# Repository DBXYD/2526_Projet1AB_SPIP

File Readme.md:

# 🐿️ Projet PAMI - Spip  (Coupe de France de Robotique)

##  Présentation de la Coupe
La **Coupe de France de Robotique** (Eurobot Open France) est une compétition annuelle organisée par **Planète Sciences**.  
Elle réunit des équipes étudiantes, associatives ou indépendantes, qui conçoivent des **robots autonomes** capables de relever des défis techniques en lien avec un thème annuel.
Depuis **plus de 10 ans**, l’association **ARES (Association de Robotique de l’ENSEA)** participe chaque année à cette compétition.  
En **2026**, la compétition se déroulera dans le cadre de la **33ᵉ édition des Rencontres de Robotique**.  
Le thème choisi est :  
> **« Winter is coming »**
Les robots auront 100 secondes pour réaliser un maximum d’actions sur une aire de jeu commune de 3 m x 2 m.
## Règlement
Le règlement complet est disponible sur le site officiel ([coupederobotique.fr](https://www.coupederobotique.fr/)), mais voici un résumé des grandes lignes :
### Aire du jeu 
Voici l’aire du jeu officielle de la Coupe de France de Robotique 2026 :

Légende :
1. Nid des écureuils  
2. Aires de départ PAMI dans le grenier  
3. Frigo  
4. Zone de chargement  
5. Zone de ramassage  
6. Garde-manger  
7. Thermomètre  
8. Curseur
### 🔹 Objectifs du thème
Les robots doivent aider les écureuils à stocker et protéger leurs noisettes en réalisant différentes actions :

1. **Gardons les noisettes au chaud !**  
   Ramasser les caisses de noisettes et les déposer dans un **garde-manger** ou dans le **nid**.  
   
2. **Trouver, c’est garder !**  
   Utiliser un petit actionneur mobile (PAMI) pour vider les **frigos** du grenier et les remplir avec des **caisses pourries**.  
   
3. **Pas trop chaud, ni trop froid.**  
   Déplacer le **curseur du thermomètre** pour régler la température au plus près du centre.  
   
4. **On est mieux dans son nid.**  
   Finir le match avec le **robot principal dans le nid**.  
   
5. **À table !**  
   Les petits écureuils (PAMIs) doivent rejoindre les **garde-mangers** et « manger » les noisettes.

Voici l'organisation principale du projet :

* 📁 **[Firmware](./Firmware/)** : Contient le code embarqué pour les microcontrôleurs, incluant l'asservissement.
* 📁 **[Hardware](./Hardware/)** : Regroupe les conceptions électroniques (PCB) et les modélisations mécaniques (3D).
* 📁 **[Datasheets](./Datasheets/)** : Contient l’ensemble des datasheets des différents composants utilisés.
* 📁 **[Strategie](./Strategie/)** : Documents et algorithmes définissant le comportement du robot pendant les matchs.
* 📁 **[Tableau de bord](./Tableau%20de%20bord/)** : Outils de monitoring et suivi des indicateurs de l'équipe.

# Rapport de projet - SPIP

## 1. Introduction

Le projet SPIP consiste à concevoir un robot PAMI pour la Coupe de France de Robotique. Le robot doit être autonome, compact, capable de se déplacer de manière contrôlée, d'interagir avec le terrain, d'éviter les obstacles et de réaliser des actions simples pendant le match.

Notre travail a donc porté sur trois grands axes :

- le choix et l'intégration des composants ;
- la conception électronique du robot avec KiCad ;
- le développement du firmware embarqué sur STM32.

Le robot est organisé autour d'une carte électronique principale. Cette carte relie le microcontrôleur, les moteurs, les encodeurs, les capteurs, les boutons, les LEDs, le connecteur de programmation et l'actionneur XL-320.

## 2. Objectif global du robot

Le robot doit pouvoir se déplacer de façon autonome sur l'aire de jeu de la Coupe de France de Robotique. Pour cela, nous avons besoin :

- d'un cerveau capable de piloter tous les périphériques ;
- de deux moteurs ;
- d'encodeurs pour connaître le déplacement réel ;
- d'un capteur ultrason pour détecter les obstacles ;
- d'un suiveur de ligne infrarouge pour corriger la trajectoire ;
- d'un servomoteur XL-320 pour actionner une partie mobile ;
- d'une carte électronique pour relier tous les éléments.

L'architecture générale est la suivante :

```mermaid
flowchart TD
    Batterie["+6 V batterie"] -->|Alimentation puissance +6 V| Driver["DRV8411<br/>Driver moteurs"]
    Batterie -->|Alimentation puissance +6 V| XL320["Dynamixel XL-320<br/>Actionneur"]
    Batterie -->|Entrée alimentation| Regulateur["Régulateur AZ1117<br/>3.3 V"]

    Regulateur -->|Alimentation logique 3.3 V| STM32["STM32G431CBU6<br/>Microcontrôleur"]
    Regulateur -->|Alimentation capteurs 3.3 V| Capteurs["Capteurs<br/>IR / ultrason / boutons / LEDs"]

    STM32 -->|Commandes PWM<br/>AIN1, AIN2, BIN1, BIN2| Driver
    Driver -->|Puissance moteur<br/>AOUT / BOUT| Moteurs["2 moteurs DC"]

    Moteurs -->|Rotation mesurée| Encodeurs["Encodeurs moteurs"]
    Encodeurs -->|Retour position / vitesse<br/>signaux A et B| STM32

    Capteurs -->|Informations terrain<br/>ligne, obstacle, boutons| STM32
    STM32 -->|UART half-duplex<br/>DATA| XL320

    STLINK["Connecteur STDC14<br/>ST-Link"] -->|Programmation / debug<br/>SWDIO, SWCLK, UART| STM32

    classDef power fill:#fff3cd,stroke:#f59f00,stroke-width:2px,color:#111;
    classDef logic fill:#dbeafe,stroke:#2563eb,stroke-width:2px,color:#111;
    classDef command fill:#fee2e2,stroke:#dc2626,stroke-width:2px,color:#111;
    classDef sensor fill:#dcfce7,stroke:#16a34a,stroke-width:2px,color:#111;
    classDef debug fill:#f3e8ff,stroke:#9333ea,stroke-width:2px,color:#111;

    class Batterie,Regulateur power;
    class STM32 logic;
    class Driver,Moteurs command;
    class Encodeurs,Capteurs sensor;
    class XL320,STLINK debug;

    linkStyle 0 stroke:#f59f00,stroke-width:2px;
    linkStyle 1 stroke:#f59f00,stroke-width:2px;
    linkStyle 2 stroke:#f59f00,stroke-width:2px;
    linkStyle 3 stroke:#2563eb,stroke-width:2px;
    linkStyle 4 stroke:#2563eb,stroke-width:2px;
    linkStyle 5 stroke:#dc2626,stroke-width:2px;
    linkStyle 6 stroke:#dc2626,stroke-width:2px;
    linkStyle 7 stroke:#16a34a,stroke-width:2px;
    linkStyle 8 stroke:#16a34a,stroke-width:2px;
    linkStyle 9 stroke:#16a34a,stroke-width:2px;
    linkStyle 10 stroke:#9333ea,stroke-width:2px;
    linkStyle 11 stroke:#9333ea,stroke-width:2px;
```

**Légende des liens :**

<div style="display: flex; flex-direction: column; gap: 6px; margin-top: 8px;">

<div style="background-color: #fff3cd; border-left: 6px solid #f59f00; padding: 8px;">
<strong>Orange</strong> : alimentation puissance <code>+6 V</code>.
</div>

<div style="background-color: #dbeafe; border-left: 6px solid #2563eb; padding: 8px;">
<strong>Bleu</strong> : alimentation logique <code>3.3 V</code>.
</div>

<div style="background-color: #fee2e2; border-left: 6px solid #dc2626; padding: 8px;">
<strong>Rouge</strong> : commande moteur et puissance moteur.
</div>

<div style="background-color: #dcfce7; border-left: 6px solid #16a34a; padding: 8px;">
<strong>Vert</strong> : retours capteurs et encodeurs vers le STM32.
</div>

<div style="background-color: #f3e8ff; border-left: 6px solid #9333ea; padding: 8px;">
<strong>Violet</strong> : programmation, debug et communication série.
</div>

</div>

## 3. Choix des composants

> **Note de conception :** Pour consulter l'inventaire complet du matériel et le détail des calculs de dimensionnement (calculs de puissance, choix des tailles de boîtiers CMS, etc.), reportez-vous au [Document de détails](./Hardware/details.md).

### 3.1 Microcontrôleur STM32G431CBU6

Nous avons choisi le **STM32G431CBU6** comme microcontrôleur principal du robot.

Datasheet : [Datasheet officielle STMicroelectronics](https://www.st.com/resource/en/datasheet/stm32g431cb.pdf)

Ce composant a été choisi car il correspond bien aux besoins du robot :

- il fonctionne en logique **3.3 V**, ce qui est adapté à notre circuit ;
- il dispose de nombreux GPIO pour connecter les capteurs, boutons, LEDs et signaux moteurs ;
- il intègre plusieurs timers, indispensables pour générer des signaux PWM et lire les encodeurs ;
- il possède des interfaces UART, utiles pour communiquer avec le XL-320 et avec le ST-Link ;
- son cœur ARM Cortex-M4 à 170 MHz offre assez de puissance pour faire tourner l'asservissement, la stratégie et les capteurs en parallèle.

Dans notre projet, le STM32 sert donc de centre de décision. Il lit les capteurs, calcule les consignes de mouvement, pilote les moteurs et exécute la stratégie de match.

### 3.2 Driver moteur DRV8411APWPR

Pour piloter les deux moteurs DC, nous avons utilisé un **DRV8411APWPR**.

Datasheet : [Datasheet Texas Instruments DRV8411](https://www.ti.com/lit/ds/symlink/drv8411.pdf)

Le STM32 ne peut pas alimenter directement les moteurs, car ses broches ne fournissent pas assez de courant. Le DRV8411 joue donc le rôle d'interface de puissance entre le microcontrôleur et les moteurs.

Nous l'avons choisi car :

- il permet de piloter deux moteurs DC avec un seul circuit ;
- il fonctionne avec des signaux logiques compatibles avec le STM32 ;
- il accepte une alimentation moteur séparée, ici le rail **+6 V** ;
- il possède une sortie de défaut, notée `FAULT`, permettant au microcontrôleur de détecter un problème ;
- il peut être commandé par des signaux PWM pour régler la vitesse.

Dans le schéma KiCad, les signaux importants sont :

- `AIN1` et `AIN2` pour le moteur A ;
- `BIN1` et `BIN2` pour le moteur B ;
- `AOUT1`, `AOUT2`, `BOUT1`, `BOUT2` vers les connecteurs moteurs ;
- `FAULT` vers le STM32 ;
- `AIPROPI` et `BIPROPI` avec des résistances pour la partie mesure/protection du driver.

### 3.3 Moteurs DC avec encodeurs

Le robot utilise deux moteurs DC avec encodeurs intégrés.

Dans le schéma KiCad, les connecteurs moteurs sont des connecteurs JST 6 broches :

- `J6` pour un moteur ;
- `J7` pour l'autre moteur.

Chaque connecteur transporte :

- les deux sorties moteur venant du driver ;
- l'alimentation de l'encodeur ;
- la masse ;
- les deux signaux encodeur A et B.

Nous avons choisi des moteurs avec encodeurs car un simple moteur DC ne permet pas de connaître la distance réelle parcourue. Avec les encodeurs, le STM32 peut compter les impulsions et en déduire :

- la distance parcourue ;
- la vitesse réelle ;
- le sens de rotation ;
- l'erreur entre la consigne et le mouvement réel.

Cela permet de faire un asservissement et d'obtenir des déplacements plus précis.

### 3.4 Servomoteur Dynamixel XL-320

Le robot utilise un **Dynamixel XL-320** comme actionneur pour une partie mobile, notamment la queue.

Datasheet : [Documentation ROBOTIS officielle](https://emanual.robotis.com/docs/en/dxl/x/xl320/)

Nous avons choisi le XL-320 car c'est un servomoteur intelligent. Contrairement à un servo simple, il intègre déjà :

- un moteur ;
- un contrôleur ;
- une électronique de puissance ;
- un protocole de communication ;
- un retour d'état.

Il se commande avec une liaison série half-duplex. Dans KiCad, il est relié par le connecteur `J3`, avec :

- `+6V` pour l'alimentation ;
- `GND` ;
- `DATA` pour la communication.

Dans le `.ioc`, la broche `PC4` est configurée en `USART1` half-duplex pour communiquer avec le XL-320.

### 3.5 Capteur ultrason HC-SR04

Le capteur ultrason est utilisé pour détecter les obstacles devant le robot.

Datasheet : [Datasheet HC-SR04 via DigiKey](https://www.digikey.com/en/htmldatasheets/production/3822706/0/0/1/hc-sr04.html)

Nous l'avons ajouté pour que le robot puisse s'arrêter lorsqu'un objet ou un autre robot se trouve trop près. Le principe est simple :

- le STM32 envoie une impulsion sur `TRIG` ;
- le capteur émet une onde ultrasonore ;
- le signal `ECHO` reste actif pendant une durée proportionnelle à la distance ;
- le STM32 mesure cette durée et calcule la distance.

Dans KiCad, le capteur est relié au connecteur `J4` :

- `+3.3V` ;
- `TRIGG` ;
- `ECHO` ;
- `GND`.

Dans le code, si la distance mesurée est inférieure à 10 cm, le robot met les deux vitesses moteur à zéro. Cela permet d'éviter une collision.

### 3.6 Suiveur de ligne infrarouge

Le suiveur de ligne infrarouge est utilisé pour détecter la position du robot par rapport à une ligne au sol.

Dans KiCad, le connecteur `J5` relie le module infrarouge au STM32 :

- `+3.3V` ;
- `X1` ;
- `X2` ;
- `X3` ;
- `X4` ;
- `GND`.

Nous avons choisi un suiveur de ligne à plusieurs sorties car il donne plus d'information qu'un seul capteur. Avec quatre signaux, le robot peut savoir si la ligne est :

- centrée ;
- décalée à gauche, légèrement ou fortement ;
- décalée à droite, légèrement ou fortement ;
- perdue ou détectée partiellement.

Dans le firmware, les valeurs des quatre capteurs sont combinées dans une variable `position`. Cette position peut ensuite être utilisée pour corriger la trajectoire du robot.

### 3.7 Régulateur AZ1117-3.3

Le régulateur **AZ1117-3.3** permet de créer le rail d'alimentation 3.3 V à partir de l'alimentation principale.

Datasheet : [Datasheet officielle AZ1117](https://www.diodes.com/assets/Datasheets/AZ1117.pdf)

Nous l'avons ajouté car le STM32 et plusieurs signaux logiques doivent être alimentés en 3.3 V, alors que la partie puissance du robot fonctionne avec une tension plus élevée, notamment le rail +6 V.

Dans KiCad, le régulateur est accompagné de condensateurs de découplage et de stabilisation. Ces condensateurs servent à limiter les variations de tension et à rendre l'alimentation plus stable.

### 3.8 Condensateurs de découplage

Le schéma KiCad contient plusieurs condensateurs :

- `100nF` près des circuits intégrés ;
- `1uF`, `10uF` et `22uF` pour stabiliser les rails d'alimentation ;
- des condensateurs autour du driver moteur et du régulateur.

Datasheets :

- [Wurth 100 nF 885012205085](https://www.we-online.com/components/products/datasheet/885012205085.pdf)
- [Wurth 10 nF 885012205067](https://www.we-online.com/components/products/datasheet/885012205067.pdf)
- [Wurth 1 uF 885012206076](https://www.we-online.com/components/products/datasheet/885012206076.pdf)
- [Wurth 22 uF 885012107019](https://www.we-online.com/components/products/datasheet/885012107019.pdf)

Ces condensateurs sont nécessaires car les moteurs et les circuits numériques peuvent créer des variations rapides de courant. Sans découplage, ces variations pourraient provoquer des resets du microcontrôleur ou des comportements instables.

### 3.9 Résistances

Le PCB utilise plusieurs résistances :

- résistances de tirage pour les boutons ;
- résistances en série avec les LEDs ;
- résistances liées au driver moteur ;
- résistance de `BOOT0` ;
- résistances de valeurs particulières comme `82k5`.

Datasheets :

- [Yageo RC0805 general purpose](https://www.yageo.com/upload/media/product/productsearch/datasheet/rchip/PYu-RC_Group_51_RoHS_L_12.pdf)
- [RS Pro 1 kOhm](https://docs.rs-online.com/21eb/0900766b8157cb45.pdf)

Les résistances de LEDs sont dimensionnées pour limiter le courant. Les annotations du schéma indiquent les tensions directes des LEDs, par exemple `1.7V @ 1mA`, `2.3V @ 1mA` ou `2.6V @ 1mA`. Le but est d'avoir des voyants visibles sans consommer trop de courant ni endommager les LEDs.

### 3.10 LEDs utilisateur

Le PCB contient plusieurs LEDs, reliées à des signaux comme :

- `LEDR` ;
- `LEDG` ;
- `LEDB`.

Datasheets :

- [LED rouge Wurth 150060RS55040](https://www.we-online.com/components/products/datasheet/150060RS55040.pdf)
- [LED verte Wurth 150060GS55040](https://www.we-online.com/components/products/datasheet/150060GS55040.pdf)
- [LED bleue Wurth 150060BS55040](https://www.we-online.com/components/products/datasheet/150060BS55040.pdf)

Nous les avons ajoutées pour faciliter les tests. Elles peuvent indiquer un état du robot, un mode de fonctionnement, une erreur ou une étape de stratégie.

### 3.11 Boutons utilisateur

Le PCB contient plusieurs boutons, associés aux signaux :

- `Button1` ;
- `Button2` ;
- `Button3`.

Ils permettent de déclencher manuellement des actions, de changer d'état ou de lancer une séquence de test. Dans le `.ioc`, ces boutons sont configurés en interruptions externes, ce qui permet au STM32 de réagir immédiatement à un appui.

### 3.12 Connecteur de programmation STDC14

Le connecteur `J2` est un connecteur **STDC14**. Il sert à programmer et déboguer le STM32 avec un ST-Link.

Documentation :

- [Documentation STDC14 / STLINK-V3](https://www.st.com/content/ccc/resource/technical/document/user_manual/group1/99/49/91/b6/b2/3a/46/e5/DM00526767/files/DM00526767.pdf/jcr:content/translations/en.DM00526767.pdf)

Il relie notamment :

- `SWDIO` ;
- `SWCLK` ;
- `NRST` ;
- `STLINK_TX` ;
- `STLINK_RX` ;
- `3.3V` ;
- `GND`.

Nous l'avons mis pour pouvoir flasher le programme, déboguer le code et utiliser une liaison UART avec l'ordinateur.

## 4. Explication du projet KiCad

Le projet KiCad se trouve dans :

- [Schéma KiCad](./Hardware/Kicad_SPIP/Kicad_SPIP.kicad_sch)
- [PCB KiCad](./Hardware/Kicad_SPIP/Kicad_SPIP.kicad_pcb)

Le schéma est organisé en blocs fonctionnels :

- alimentation générale ;
- STM32G431CBU6 ;
- driver + moteurs ;
- servo XL-320 ;
- ultrason ;
- infrarouge ;
- boutons ;
- LEDs ;
- programmateur ;
- trous de fixation.

Cette organisation permet de comprendre rapidement le rôle de chaque partie.

### 4.1 Bloc alimentation

Le bloc alimentation sépare deux niveaux de tension :

- `+6V` pour les éléments de puissance, comme les moteurs et le XL-320 ;
- `+3.3V` pour le STM32 et les signaux logiques.

Le régulateur transforme la tension principale en 3.3 V. Des condensateurs sont placés autour des rails d'alimentation pour éviter les chutes de tension lors des appels de courant.

### 4.2 Bloc STM32

Le STM32 est au centre du schéma. Les pins sont nommées selon leur rôle logiciel :

- `PA0-US_TRIG` ;
- `PA1-US_ECHO_INT` ;
- `PA4-X1_INT` à `PA7-X4_INT` ;
- `PC4-UART_XL320` ;
- `PB10-MotorFault` ;
- `PB4/PB5` pour l'encodeur du moteur A ;
- `PB6/PB7` pour l'encodeur du moteur B ;
- `PA15/PB3/PA9/PA10` pour les PWM moteur ;
- `PA13/PA14` pour le debug SWD.

Le fait de nommer les signaux directement dans KiCad rend le schéma plus lisible et facilite la correspondance avec le fichier `.ioc`.

### 4.3 Bloc driver moteur

Le bloc moteur contient le DRV8411 et les connecteurs moteurs. Le STM32 envoie des signaux PWM au driver, et le driver fournit le courant aux moteurs.

Nous avons séparé la partie commande et la partie puissance :

- le STM32 commande avec des signaux logiques ;
- le driver gère le courant moteur ;
- les encodeurs renvoient l'information de mouvement au STM32.

Cette séparation est indispensable, car elle protège le microcontrôleur et permet un pilotage plus précis.

### 4.4 Bloc programmateur

Le connecteur STDC14 sert à relier le ST-Link pour flasher le programme et déboguer le code. 

Il permet d'accéder directement aux signaux de programmation `SWDIO` et `SWCLK`, ainsi qu'aux broches UART du STM32 pour envoyer des données vers l'ordinateur pendant les tests.

### 4.5 Bloc servomoteur intelligent

Ce bloc contient le connecteur pour le servomoteur Dynamixel XL-320. 

Le connecteur est relié au rail `+6V` pour la puissance et utilise la broche `PC4` configurée en UART half-duplex pour l'échange de données. Cette configuration permet de commander la position de l'actionneur avec un seul fil de signal.

### 4.6 Bloc capteurs

Le bloc capteurs regroupe l'ultrason et les capteurs infrarouges.

L'ultrason est utilisé pour l'évitement d'obstacles. Les capteurs infrarouges servent à suivre une ligne ou à détecter un décalage latéral.

Dans le PCB, ces capteurs sont connectés par des JST. Cela permet de démonter ou remplacer facilement un capteur sans ressouder la carte.

### 4.7 Bloc interface utilisateur

Les boutons et les LEDs permettent de tester le robot sans avoir besoin de modifier le code à chaque fois. Les boutons peuvent lancer des actions, et les LEDs peuvent afficher l'état du robot.

Ce bloc est utile pendant les phases de debug, car il donne un retour visuel immédiat.

### 4.8 Routage du PCB

Dans le PCB, les composants principaux sont placés de manière à limiter les longueurs de pistes :

- le STM32 est proche des signaux logiques ;
- le driver moteur est proche des connecteurs moteurs ;
- les connecteurs capteurs sont en bord de carte pour faciliter le câblage ;
- les trous de fixation permettent une intégration propre dans le châssis.

Les rails `GND`, `+3.3V` et `+6V` sont clairement séparés dans les nets KiCad. Cela permet de distinguer la puissance moteur de la logique microcontrôleur.
## 5. Configuration STM32CubeIDE et fichier `.ioc`

Le fichier de configuration est :

- [Firware_SPIP.ioc](./Firmware/Firware_SPIP/Firware_SPIP.ioc)

Ce fichier relie la conception électronique au code embarqué. Il indique quel pin du microcontrôleur correspond à chaque fonction.

### 5.1 Horloge

Le STM32 est configuré avec une fréquence système de **170 MHz**. Cette fréquence permet d'avoir assez de précision pour :

- les PWM moteurs ;
- la mesure ultrason ;
- les timers d'interruption ;
- l'asservissement.

### 5.2 TIM2 pour les PWM moteurs

Le timer `TIM2` est utilisé avec quatre canaux PWM :

- `TIM2_CH1` : `MotorA_PWM_Forward` ;
- `TIM2_CH2` : `MotorA_PWM_Reverse` ;
- `TIM2_CH3` : `MotorB_PWM_Forward` ;
- `TIM2_CH4` : `MotorB_PWM_Reverse`.

Ce choix permet de gérer le sens et la vitesse des deux moteurs. Chaque moteur a deux commandes, une pour le sens avant et une pour le sens arrière.

### 5.3 TIM3 et TIM4 pour les encodeurs

Les timers `TIM3` et `TIM4` sont configurés en mode encodeur :

- `TIM3` lit l'encodeur du moteur A ;
- `TIM4` lit l'encodeur du moteur B.

Le mode encodeur permet au microcontrôleur de compter automatiquement les impulsions A/B des encodeurs, ce qui donne une mesure fiable du mouvement.

### 5.4 TIM1 pour l'ultrason

Le timer `TIM1` est utilisé pour mesurer la durée du signal `ECHO` du capteur ultrason. Son prescaler permet d'obtenir une base de temps adaptée à la mesure en microsecondes.

Cette mesure est ensuite convertie en distance.

### 5.5 TIM6 comme ordonnanceur périodique

Le timer `TIM6` déclenche régulièrement une interruption. Dans cette interruption, le programme :

- déclenche l'ultrason ;
- met à jour le suiveur de ligne ;
- met à jour les encodeurs ;
- met à jour l'asservissement ;
- met à jour le mouvement ;
- remet périodiquement à zéro l'erreur cumulée du correcteur.

Cela permet de faire fonctionner plusieurs sous-systèmes en parallèle.

### 5.6 USART1 pour le XL-320

`USART1` est configuré en half-duplex sur `PC4`. Cela correspond au fonctionnement du XL-320, qui utilise une seule ligne de données pour envoyer et recevoir.

### 5.7 USART2 pour le ST-Link

`USART2` utilise `PA2` et `PA3`. Cette liaison peut servir au debug avec le ST-Link, par exemple pour afficher des informations sur un terminal série.

### 5.8 Interruptions externes

Plusieurs pins sont configurées en interruptions :

- `US_ECHO_INT` pour détecter les fronts du signal ultrason ;
- `MotorFault` pour détecter un problème driver ;
- les boutons utilisateur.

Les interruptions permettent de réagir rapidement à des événements sans attendre la boucle principale.

## 6. Explication du firmware

Le code embarqué se trouve dans :

- [Core/Src](./Firmware/Firware_SPIP/Core/Src)
- [Core/Inc](./Firmware/Firware_SPIP/Core/Inc)

Le firmware est séparé en modules. Chaque module gère une partie précise du robot.

### 6.1 `motor.c` et `motor.h`

Le module moteur gère le PWM appliqué aux moteurs. Il transforme une consigne de vitesse finale en rapport cyclique PWM.

Nous avons séparé ce module car le pilotage bas niveau des moteurs doit être indépendant de la stratégie. La stratégie dit au robot quoi faire, tandis que `motor.c` applique physiquement la puissance aux moteurs.

### 6.2 `encoder.c` et `encoder.h`

Le module encodeur lit les compteurs des timers en mode encodeur. Il calcule les variations de ticks entre deux appels.

Ces ticks sont essentiels pour connaître le mouvement réel. Sans encodeur, le robot pourrait dériver à cause des différences entre les moteurs, du frottement ou de la batterie.

### 6.3 `control.c` et `control.h`

Le module d'asservissement compare la vitesse demandée avec la vitesse mesurée par les encodeurs.

Le code calcule une erreur :

```c
error = control->ref_speed - 1000 * encoder->delta_ticks;
```

Puis il applique une correction proportionnelle et intégrale :

```c
motor->speed_final = control->ref_speed
                   + (control->Kp * error)
                   + (control->Ki * control->error_cumul);
```

Nous avons utilisé ce principe car les deux moteurs ne tournent jamais exactement pareil. L'asservissement permet de corriger les écarts et d'obtenir un mouvement plus régulier.

### 6.4 `move.c` et `move.h`

Le module mouvement gère les ordres de haut niveau :

- avancer d'une certaine distance ;
- tourner d'un certain angle ;
- s'arrêter ;
- s'arrêter en cas d'obstacle ultrason.

La fonction `move_forward` convertit une distance en centimètres en ticks encodeur. Pour cela, on utilise le périmètre de la roue :

```c
float perimeter_cm = 2.0f * M_PI * move->radius;
float K = encoder->cnt_tr / perimeter_cm;
move->d_target_cnt = d_target_cm * K;
```

Cette conversion permet de donner des ordres simples en centimètres tout en utilisant les encodeurs en interne.

### 6.5 Correction par suiveur de ligne

Le suiveur de ligne est lu régulièrement dans l'interruption du timer grâce à `LF_Update(&h_lineFollower)`. Cette fonction met à jour la position détectée par les quatre capteurs infrarouges.

Cette position est ensuite transmise à `move_update` grâce à l'appel suivant dans `main.c` :

```c
move_update(&move, &control_left, &control_right,
            &encoder_left, &encoder_right,
            &us_sensor, &h_lineFollower);
```

### 6.6 `Line_Follower.c` et `Line_Follower.h`

Le module suiveur de ligne lit les quatre entrées infrarouges :

```c
lf->position = lf->sensor_values[0] * 1000
             + lf->sensor_values[1] * 100
             + lf->sensor_values[2] * 10
             + lf->sensor_values[3];
```

Cette méthode permet de transformer quatre lectures digitales en une seule valeur facile à comparer. Par exemple :

- `0110` devient `110`, considéré comme centre ;
- `1000` indique une détection à gauche ;
- `0001` indique une détection à droite.

### 6.7 `Ultrasound.c` et `Ultrasound.h`

Le module ultrason gère le capteur HC-SR04. Il déclenche le capteur, mesure le temps du signal echo et calcule la distance.

Dans `move_update`, la sécurité obstacle est prioritaire :

```c
if (us_sensor->distance_cm > 0.0f && us_sensor->distance_cm < 10.0f) {
    control_set_speed(control_left, 0);
    control_set_speed(control_right, 0);
    return;
}
```

Nous avons fait cela pour que le robot s'arrête immédiatement si un obstacle est trop proche.

### 6.8 `xl320.c` et `xl320.h`

Le module XL-320 initialise et commande le servomoteur Dynamixel.

Dans `main.c`, le XL-320 est initialisé avec l'UART puis configuré :

```c
XL320_Init(&huart1);
XL320_Config_LowPower(254);
XL320_SetSpeed(254, 300);
```

L'identifiant `254` correspond à un broadcast, ce qui permet d'envoyer une commande à tous les servos connectés.

### 6.9 `strategy.c` et `strategy.h`

Le module stratégie définit plusieurs séquences d'actions : `strat_one`, `strat_two`, `strat_three`, `strat_four` et `strat_five`.

Chaque stratégie correspond à un enchaînement différent de déplacements. La fonction reçoit aussi une couleur, par exemple `"yellow"` ou `"blue"`, afin d'adapter le sens du virage selon le côté du terrain.

La stratégie utilisée actuellement dans `main.c` est :

```c
strat_two(&status, "yellow");
```

Nous avons choisi une machine à états car elle permet de décrire clairement la séquence de match. Chaque état correspond à une action précise : avancer, attendre la fin du déplacement, tourner, attendre la fin du virage, puis passer à l'action suivante.

### 6.10 `main.c`

Le fichier `main.c` initialise tous les modules :

- capteur ultrason ;
- suiveur de ligne ;
- moteurs ;
- encodeurs ;
- mouvement ;
- asservissement ;
- stratégie ;
- XL-320.

Avant d'entrer dans la boucle principale, le programme utilise aussi une condition de départ liée au capteur ultrason :

```c
while (us_sensor.distance_cm < 10) {
    US_Update(&us_sensor);
    HAL_Delay(50);
}
```

Cette partie joue le rôle de tirette ou de condition de départ : le robot attend que la distance mesurée soit suffisante avant de lancer sa stratégie.

La boucle principale appelle actuellement la stratégie `strat_two` avec la couleur `"yellow"`, ainsi que le mouvement de la queue :

```c
while (1)
{
    strat_two(&status, "yellow");
    move_tail(&status_tail);
}
```

La couleur passée à la fonction permet d'adapter le sens du virage selon le côté de départ du robot. Les mises à jour rapides sont faites dans l'interruption de `TIM6`, ce qui permet de garder un comportement régulier.

## 7. Résumé

Nous avons séparé le code en modules pour rendre le projet plus lisible et plus facile à tester.

Chaque fichier a une responsabilité :

- `motor` pilote le PWM ;
- `encoder` lit les ticks ;
- `control` fait l'asservissement ;
- `move` gère les distances et les rotations ;
- `Line_Follower` lit les capteurs IR ;
- `Ultrasound` mesure les distances ;
- `xl320` commande le servomoteur ;
- `strategy` décide les actions ;
- `main` initialise et orchestre le système.

Ce découpage évite d'avoir tout le code dans un seul fichier et facilite les corrections.

## 8. Conclusion

Le projet SPIP combine une partie électronique, une partie mécanique et une partie logicielle. La carte KiCad a été conçue pour centraliser les connexions du robot autour du STM32G431CBU6. Le choix des composants répond aux besoins principaux : puissance moteur, mesure de position, détection d'obstacle, suivi de ligne, communication avec le servomoteur et debug.

Le firmware transforme cette architecture matérielle en comportement autonome. Les encodeurs permettent de mesurer le mouvement, l'asservissement corrige les erreurs de vitesse, le suiveur infrarouge prépare la correction de trajectoire, l'ultrason évite les obstacles, et la stratégie enchaîne les actions du robot.

L'ensemble du travail permet d'obtenir une base de robot autonome capable de se déplacer, se corriger, réagir à son environnement et exécuter une séquence de match.

## 9. Demonstration

Voici une vidéo de notre PAMI se dirigeaant vers un des gardes manger

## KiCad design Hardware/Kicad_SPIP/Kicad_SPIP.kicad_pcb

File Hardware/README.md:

# ⚙️ Hardware & Conception

Ce dossier contient tous les éléments physiques de Spip.

## 🔌 Électronique
- **Alimentation** : Batterie Lipo (7.4V pour le XL320, régulé 3.3V pour le STM32).
- **Drivers** : Driver moteur DC (pont en H) et bus Dynamixel pour le XL320.
- **Schémas** : Voir le fichier `schema_cablage.pdf` dans ce dossier.

## 🔩 Mécanique
- **Châssis** : Découpe laser ou impression 3D.
- **Queue** : Pièce spécifique montée sur l'axe du XL320.
- **Roues** : 2 roues motrices + 1 roue folle à l'arrière.

## 📦 Liste de composants (BOM)
- 1x STM32G431CBU6
- 2x Moteurs à encodeurs
- 1x Robotis Dynamixel XL320
- 1x Capteur Ultrason HC-SR04 (ou équivalent)
- 1x Capteur de couleur
- 3x Capteurs de ligne (Infrarouge)

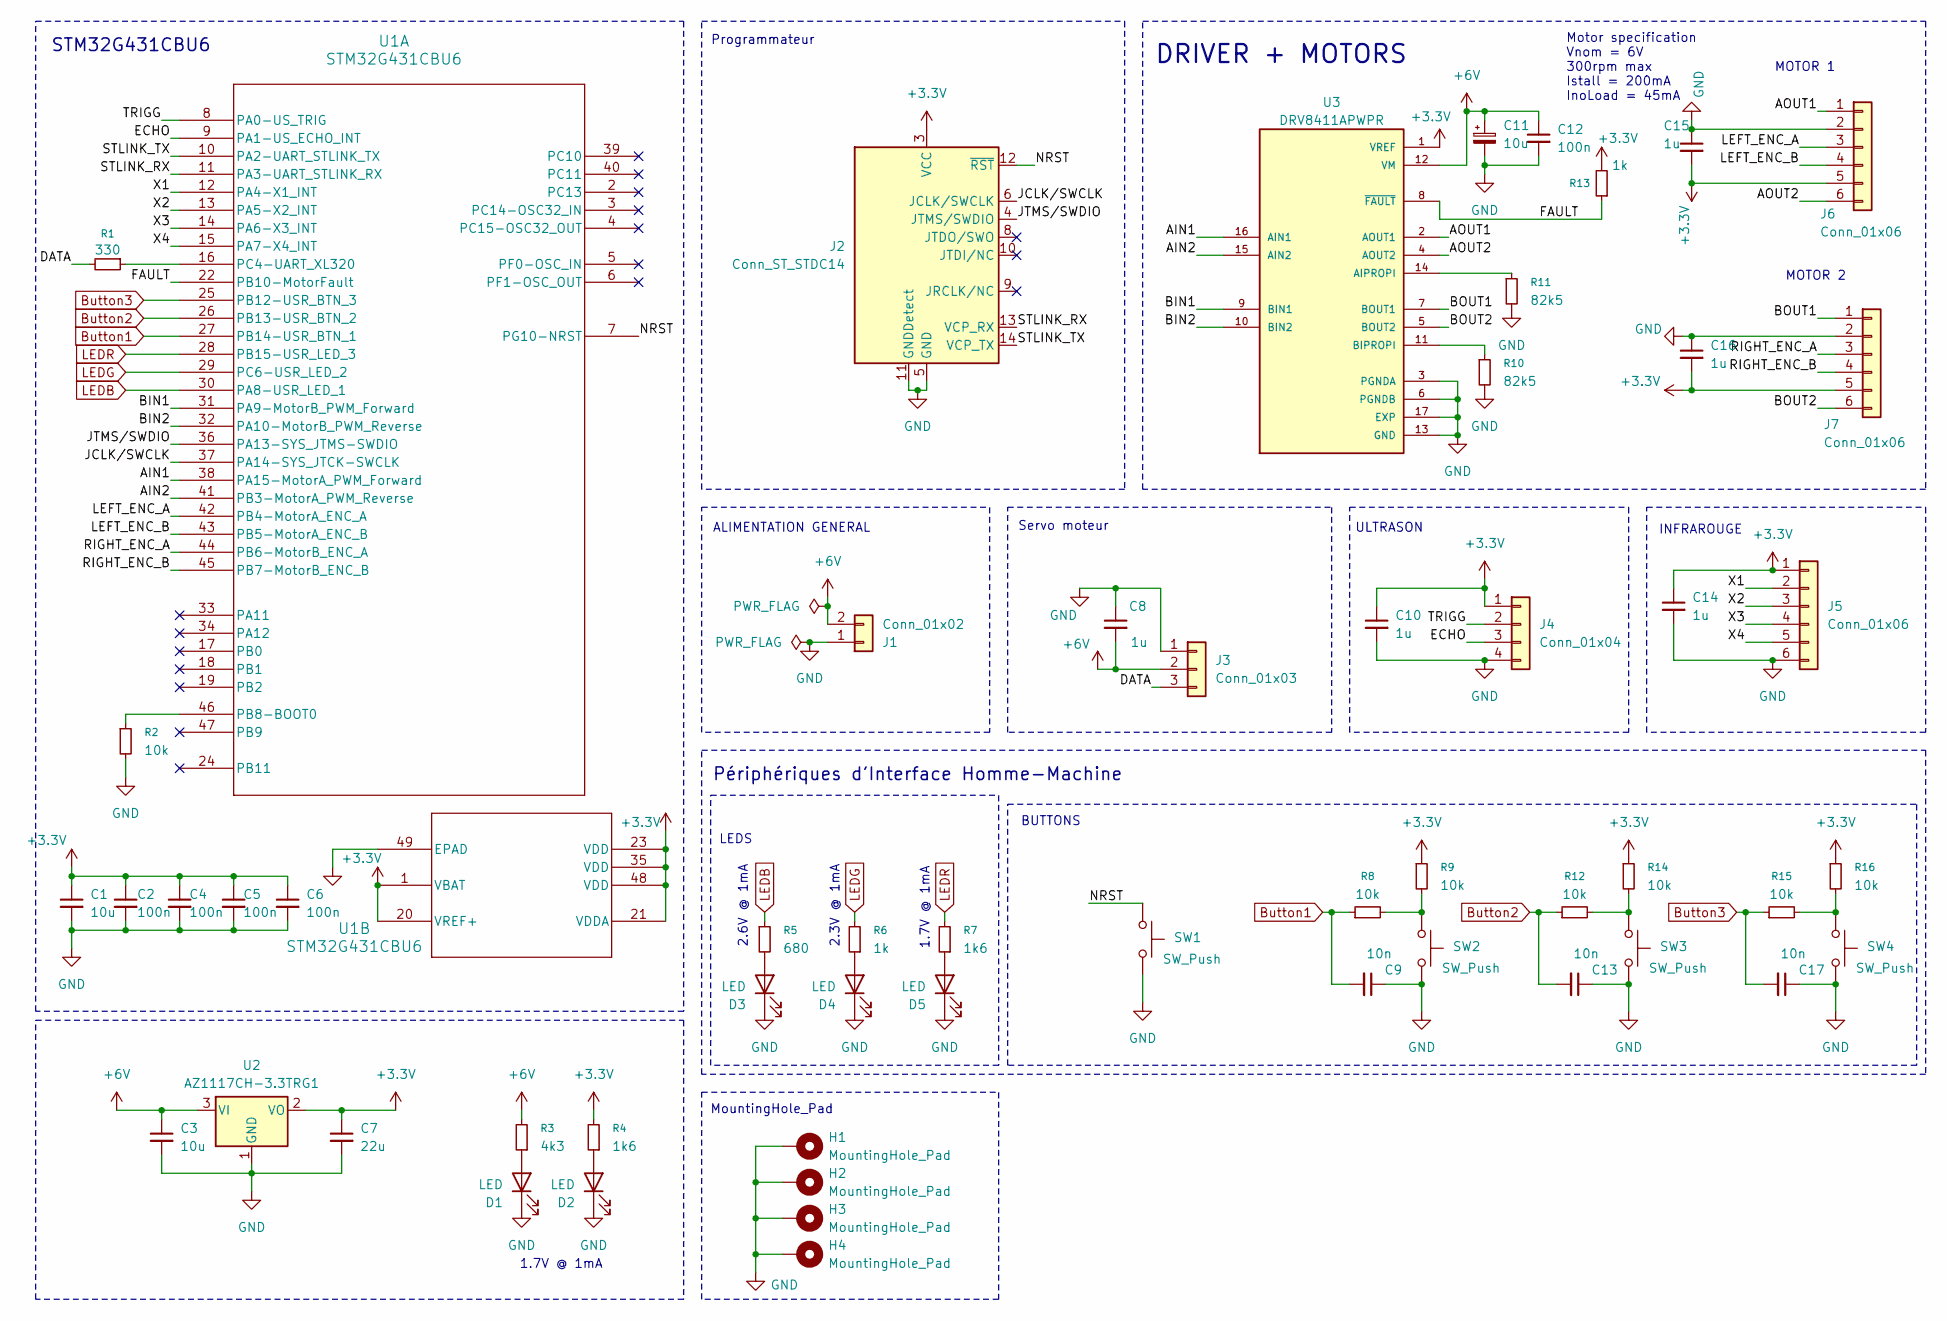
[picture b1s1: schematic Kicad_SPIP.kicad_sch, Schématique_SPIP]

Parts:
C1, C3: 10u; C_0603_1608Metric
C2, C4, C5, C6, C12: 100n; C_0402_1005Metric
C7: 22u; C_0805_2012Metric
C8, C10, C14, C15, C16: 1u; C_0603_1608Metric
C9, C13, C17: 10n; C_0402_1005Metric
C11: 10u; CP_Elec_4x5.4
D1, D2, D5: LED; LED_0603_1608Metric; MPN 150060RS55040
D3: LED; LED_0603_1608Metric; MPN 150060BS55040
D4: LED; LED_0603_1608Metric; MPN 150060GS55040
H1, H2, H3, H4: MountingHole_Pad; MountingHole_3.2mm_M3_Pad_Via
J1: Conn_01x02; JST_XH_B2B-XH-A_1x02_P2.50mm_Vertical
J2: Conn_ST_STDC14; PinHeader_2x07_P1.27mm_Vertical_SMD
J3: Conn_01x03; JST_PH_B3B-PH-K_1x03_P2.00mm_Vertical
J4: Conn_01x04; JST_PH_B4B-PH-K_1x04_P2.00mm_Vertical
J5, J6, J7: Conn_01x06; JST_PH_B6B-PH-K_1x06_P2.00mm_Vertical
R1: 330; R_0402_1005Metric
R2, R8, R9, R12, R14, R15, R16: 10k; R_0402_1005Metric
R3: 4k3; R_0402_1005Metric
R4, R7: 1k6; R_0402_1005Metric
R5: 680; R_0402_1005Metric
R6, R13: 1k; R_0402_1005Metric
R10, R11: 82k5; R_0402_1005Metric
SW1, SW2, SW3, SW4: SW_Push; SW_SPST_B3U-3000P
U1: STM32G431CBU6; UFQFPN-48_7X7X0P55MM
U2: AZ1117CH-3.3TRG1; SOT-223-3_TabPin2
U3: DRV8411APWPR; IC_DRV8411APWPR; MPN DRV8411APWPR

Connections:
+3.3V: C1.1, C2.1, C4.1, C5.1, C6.1, C7.1, C10.1, C14.1, C15.2, C16.2, J2.3 (VCC), J4.1, J5.1, J6.5, J7.5, R4.2, R9.1, R13.2, R14.1, R16.1, U1.1 (VBAT), U1.20 (VREF+), U1.21 (VDDA), U1.23 (VDD), U1.35 (VDD), U1.48 (VDD), U2.2 (VO), U3.1 (VREF)
+6V: C3.1, C8.2, C11.1, C12.1, J1.2, J3.2, R3.2, U2.3 (VI), U3.12 (VM)
/AIN1: U1.38 (PA15-MotorA_PWM_Forward), U3.16 (AIN1)
/AIN2: U1.41 (PB3-MotorA_PWM_Reverse), U3.15 (AIN2)
/AOUT1: J6.1, U3.2 (AOUT1)
/AOUT2: J6.6, U3.4 (AOUT2)
/BIN1: U1.31 (PA9-MotorB_PWM_Forward), U3.9 (BIN1)
/BIN2: U1.32 (PA10-MotorB_PWM_Reverse), U3.10 (BIN2)
/BOUT1: J7.1, U3.7 (BOUT1)
/BOUT2: J7.6, U3.5 (BOUT2)
/DATA: J3.3, R1.2
/ECHO: J4.3, U1.9 (PA1-US_ECHO_INT)
/FAULT: R13.1, U1.22 (PB10-MotorFault), U3.8 (~FAULT)
/JCLK/SWCLK: J2.6 (JCLK/SWCLK), U1.37 (PA14-SYS_JTCK-SWCLK)
/JTMS/SWDIO: J2.4 (JTMS/SWDIO), U1.36 (PA13-SYS_JTMS-SWDIO)
/LEFT_ENC_A: J6.3, U1.42 (PB4-MotorA_ENC_A)
/LEFT_ENC_B: J6.4, U1.43 (PB5-MotorA_ENC_B)
/NRST: J2.12 (~RST), SW1.2, U1.7 (PG10-NRST)
/RIGHT_ENC_A: J7.3, U1.44 (PB6-MotorB_ENC_A)
/RIGHT_ENC_B: J7.4, U1.45 (PB7-MotorB_ENC_B)
/STLINK_RX: J2.13 (VCP_RX), U1.11 (PA3-UART_STLINK_RX)
/STLINK_TX: J2.14 (VCP_TX), U1.10 (PA2-UART_STLINK_TX)
/TRIGG: J4.2, U1.8 (PA0-US_TRIG)
/X1: J5.2, U1.12 (PA4-X1_INT)
/X2: J5.3, U1.13 (PA5-X2_INT)
/X3: J5.4, U1.14 (PA6-X3_INT)
/X4: J5.5, U1.15 (PA7-X4_INT)
Button1: C9.2, R8.1, U1.27 (PB14-USR_BTN_1)
Button2: C13.2, R12.1, U1.26 (PB13-USR_BTN_2)
Button3: C17.2, R15.1, U1.25 (PB12-USR_BTN_3)
GND: C1.2, C2.2, C3.2, C4.2, C5.2, C6.2, C7.2, C8.1, C9.1, C10.2, C11.2, C12.2, C13.1, C14.2, C15.1, C16.1, C17.1, D1.1 (K), D2.1 (K), D3.1 (K), D4.1 (K), D5.1 (K), H1.1, H2.1, H3.1, H4.1, J1.1, J2.5 (GND), J2.7 (GND), J2.11 (GNDDetect), J3.1, J4.4, J5.6, J6.2, J7.2, R2.2, R10.2, R11.2, SW1.1, SW2.1, SW3.1, SW4.1, U1.49 (EPAD), U2.1 (GND), U3.3 (PGNDA), U3.6 (PGNDB), U3.13 (GND), U3.17 (EXP)
LEDB: R5.1, U1.30 (PA8-USR_LED_1)
LEDG: R6.2, U1.29 (PC6-USR_LED_2)
LEDR: R7.2, U1.28 (PB15-USR_LED_3)
unnamed: D1.2 (A), R3.1
unnamed: D2.2 (A), R4.1
unnamed: D3.2 (A), R5.2
unnamed: D4.2 (A), R6.1
unnamed: D5.2 (A), R7.1
unnamed: R8.2, R9.2, SW2.2
unnamed: R12.2, R14.2, SW3.2
unnamed: R15.2, R16.2, SW4.2
unnamed: R2.1, U1.46 (PB8-BOOT0)
unnamed: R1.1, U1.16 (PC4-UART_XL320)
unnamed: R11.1, U3.14 (AIPROPI)
unnamed: R10.1, U3.11 (BIPROPI)

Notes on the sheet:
2.3V @ 1mA
DRIVER + MOTORS
Motor specification Vnom = 6V 300rpm max Istall = 200mA InoLoad = 45mA
Servo moteur
LEDS
STM32G431CBU6
Périphériques d'Interface Homme-Machine
2.6V @ 1mA
MOTOR 1
Programmateur
1.7V @ 1mA
ULTRASON
ALIMENTATION GENERAL
INFRAROUGE
BUTTONS
MOTOR 2
MountingHole_Pad

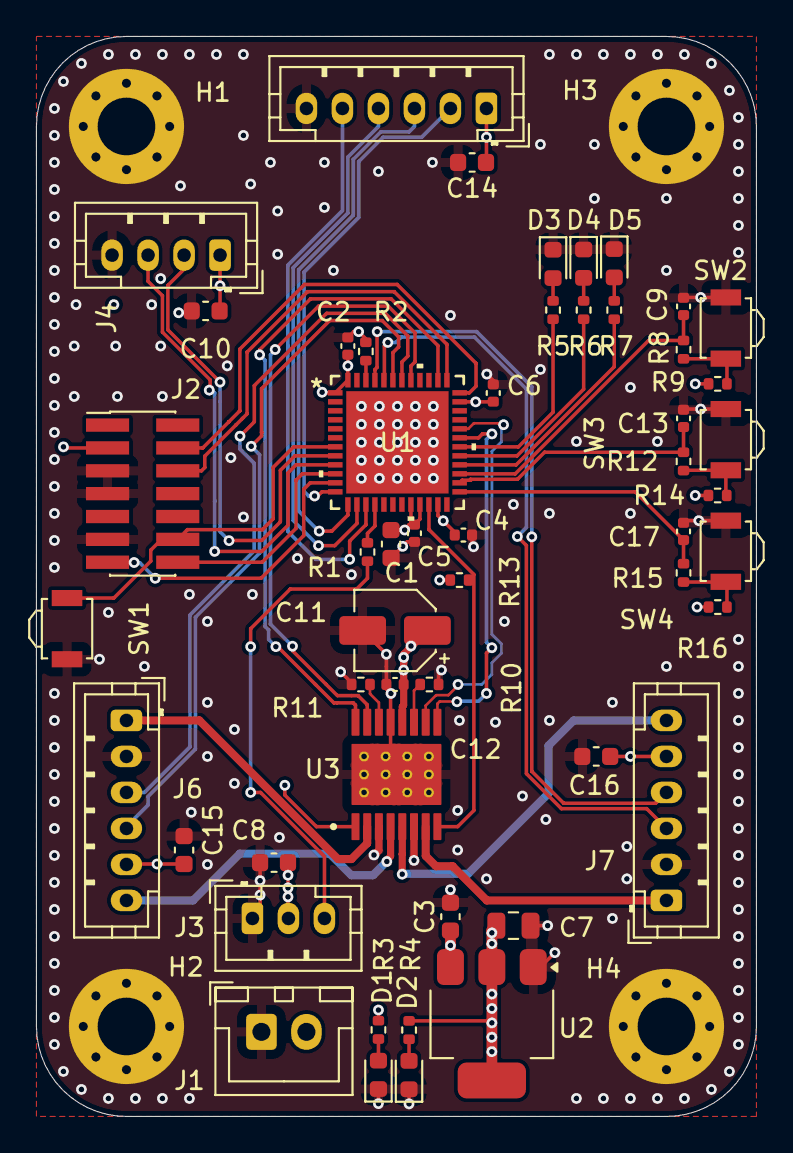
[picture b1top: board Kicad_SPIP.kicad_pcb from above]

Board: 4 copper layers, 40.0 x 60.0 mm, 56 parts (0 on the bottom side), 46 nets.

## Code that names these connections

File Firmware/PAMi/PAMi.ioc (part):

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Mcu.Name=STM32G431C(6-8-B)Ux
Mcu.Package=UFQFPN48
Mcu.UserName=STM32G431CBUx
PA0.GPIOParameters=GPIO_Label
PA0.GPIO_Label=US_TRIG
PA0.Signal=GPIO_Output
PA1.GPIOParameters=GPIO_Label
PA1.GPIO_Label=US_ECHO_INT
PA1.Signal=GPXTI1
PA10.GPIOParameters=GPIO_Label
PA10.GPIO_Label=MotorB_PWM_Reverse
PA10.Signal=S_TIM2_CH4
PA13.Mode=Serial_Wire
PA13.Signal=SYS_JTMS-SWDIO
PA14.Mode=Serial_Wire
PA14.Signal=SYS_JTCK-SWCLK
PA15.GPIOParameters=GPIO_Label
PA15.GPIO_Label=MotorA_PWM_Forward
PA15.Signal=S_TIM2_CH1
PA2.GPIOParameters=GPIO_Label
PA2.GPIO_Label=UART_STLINK_TX
PA2.Mode=Asynchronous
PA2.Signal=USART2_TX
PA3.GPIOParameters=GPIO_Label
PA3.GPIO_Label=UART_STLINK_RX
PA3.Mode=Asynchronous
PA3.Signal=USART2_RX
PA4.GPIOParameters=GPIO_Label
PA4.GPIO_Label=X1_INT
PA4.Signal=GPXTI4
PA5.GPIOParameters=GPIO_Label
PA5.GPIO_Label=X2_INT
PA5.Signal=GPXTI5
PA6.GPIOParameters=GPIO_Label
PA6.GPIO_Label=X3_INT
PA6.Signal=GPXTI6
PA7.GPIOParameters=GPIO_Label
PA7.GPIO_Label=X4_INT
PA7.Signal=GPXTI7
PA8.GPIOParameters=GPIO_Label
PA8.GPIO_Label=USR_LED_1
PA8.Signal=GPIO_Output
PA9.Signal=S_TIM2_CH3
PB10.GPIOParameters=GPIO_Label
PB10.GPIO_Label=MotorFault
PB10.Signal=GPXTI10
PB12.GPIOParameters=GPIO_Label
PB12.GPIO_Label=USR_BTN_3
PB12.Signal=GPXTI12
PB13.GPIOParameters=GPIO_Label
PB13.GPIO_Label=USR_BTN_2
PB13.Signal=GPXTI13
PB14.GPIOParameters=GPIO_Label
PB14.GPIO_Label=USR_BTN_1
PB14.Signal=GPXTI14
PB15.GPIOParameters=GPIO_Label
PB15.GPIO_Label=USR_LED_3
PB15.Signal=GPIO_Output
PB3.Signal=S_TIM2_CH2
PB4.GPIOParameters=GPIO_Label
PB4.GPIO_Label=MotorA_ENC_A
PB4.Signal=S_TIM3_CH1
PB5.GPIOParameters=GPIO_Label
PB5.GPIO_Label=MotorA_ENC_B
PB5.Signal=S_TIM3_CH2
PB6.GPIOParameters=GPIO_Label
PB6.GPIO_Label=MotorB_ENC_A
PB6.Signal=S_TIM4_CH1
PB7.GPIOParameters=GPIO_Label
PB7.GPIO_Label=MotorB_ENC_B
PB7.Signal=S_TIM4_CH2
PC4.GPIOParameters=GPIO_Label
PC4.GPIO_Label=UART_XL320
PC4.Mode=Half_duplex(single_wire_mode)
PC4.Signal=USART1_TX
PC6.GPIOParameters=GPIO_Label
PC6.GPIO_Label=USR_LED_2
PC6.Signal=GPIO_Output
RCC.HSE_VALUE=8000000
RCC.SYSCLKFreq_VALUE=170000000
RCC.SYSCLKSource=RCC_SYSCLKSOURCE_PLLCLK
board=custom

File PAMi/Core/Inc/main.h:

/* USER CODE BEGIN Header */
/**
  ******************************************************************************
  * @file           : main.h
  * @brief          : Header for main.c file.
  *                   This file contains the common defines of the application.
  ******************************************************************************
  * @attention
  *
  * Copyright (c) 2026 STMicroelectronics.
  * All rights reserved.
  *
  * This software is licensed under terms that can be found in the LICENSE file
  * in the root directory of this software component.
  * If no LICENSE file comes with this software, it is provided AS-IS.
  *
  ******************************************************************************
  */
/* USER CODE END Header */

/* Define to prevent recursive inclusion -------------------------------------*/
#ifndef __MAIN_H
#define __MAIN_H

#ifdef __cplusplus
extern "C" {
#endif

/* Includes ------------------------------------------------------------------*/
#include "stm32g4xx_hal.h"

/* Private includes ----------------------------------------------------------*/
/* USER CODE BEGIN Includes */

/* USER CODE END Includes */

/* Exported types ------------------------------------------------------------*/
/* USER CODE BEGIN ET */

/* USER CODE END ET */

/* Exported constants --------------------------------------------------------*/
/* USER CODE BEGIN EC */

/* USER CODE END EC */

/* Exported macro ------------------------------------------------------------*/
/* USER CODE BEGIN EM */

/* USER CODE END EM */

void HAL_TIM_MspPostInit(TIM_HandleTypeDef *htim);

/* Exported functions prototypes ---------------------------------------------*/
void Error_Handler(void);

/* USER CODE BEGIN EFP */

/* USER CODE END EFP */

/* Private defines -----------------------------------------------------------*/
#define BIN1_Pin GPIO_PIN_2
#define BIN1_GPIO_Port GPIOA
#define BIN2_Pin GPIO_PIN_3
#define BIN2_GPIO_Port GPIOA
#define X1_Pin GPIO_PIN_4
#define X1_GPIO_Port GPIOA
#define X2_Pin GPIO_PIN_5
#define X2_GPIO_Port GPIOA
#define X3_Pin GPIO_PIN_6
#define X3_GPIO_Port GPIOA
#define X4_Pin GPIO_PIN_7
#define X4_GPIO_Port GPIOA
#define AIN1_Pin GPIO_PIN_11
#define AIN1_GPIO_Port GPIOA
#define AIN2_Pin GPIO_PIN_12
#define AIN2_GPIO_Port GPIOA

/* USER CODE BEGIN Private defines */

/* USER CODE END Private defines */

#ifdef __cplusplus
}
#endif

#endif /* __MAIN_H */

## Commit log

2026-02-05 Datasheets
2026-02-05 premier commit
2026-02-07 Create Branchement MicroC
2026-02-07 Ajout du PDF dynamixel_xl-320
2026-02-08 modification
2026-02-08 Modification du readme.md
2026-02-08 modif
2026-02-08 modificatio
2026-02-09 ajout de la datasheeet du drive
2026-02-09 ajout du pcb et du driver à la datasheet
2026-02-12 Nouvelle version du Kicad
2026-02-12 Fichier IOC
2026-02-12 Nouveau schéma Kicad
2026-02-12 rajout fichier des composants et des empreintes
2026-02-12 correction du markdown
2026-02-12 mise à jour des pin du code
2026-02-19 mise à jour de la schématique du PCB
2026-02-19 Mise à jour du journal de board
2026-02-19 mise à jour des pins
2026-02-19 suppression fichier branchement pins ancien
2026-02-19 modification de la page d'acceuil
2026-02-19 Ajout de nouveaux composants
2026-02-19 pcb 1.2
2026-02-19 mise à jour du journal de booard
2026-02-19 mise à jour du journal de bord
2026-02-19 mise à jour du journal de bord
2026-02-19 pcb rootage
2026-02-19 derniere version du PCB Layout
2026-02-20 ajout de la nouvelle liste des commande
2026-03-13 code encoder & moteur v1
2026-03-18 pin ultrason Kicad déplacé & code encoder & moteur v2
2026-03-23 code encoder & motor v3
2026-03-23 code encoder & moter v3
2026-03-26 moteurv4
2026-03-27 encoder & moter v5
2026-04-03 encoder & moter v6
2026-04-09 spip mise en commun
2026-04-09 version anglaise plus stratégie
2026-04-09 xl320 et arret en cas d'obstacle + journal de la sceance
2026-05-19 journal de bord
2026-05-19 Explication Kicad
2026-05-19 Explication Kicad markdown
2026-05-20 code avec toute les stratégies et le système de tirette
2026-05-20 Journal Rayan
2026-05-20 Update journal Rayan
2026-05-22 Ajoute la correction du suiveur de ligne
2026-05-23 modifiacation du rapport et ajout de fichier pour le rapport
2026-05-23 modifiacation dans le rapport
